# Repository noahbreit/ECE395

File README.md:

# ECE395
motor inverter project

# Start-Up Procedure
Step,Operation,Parameter,Value,Description
1,SAP,0,"1, 2, or 3",Set Motor Type 
2,SAP,4,3,Select Open-Loop Voltage Mode 
3,SAP,53,1,Enable Direct Velocity Mode 
4,SAP,47,[1000],Set Base Voltage/Duty Cycle 
5,SAP,124,[Speed],Set Target Velocity to Start

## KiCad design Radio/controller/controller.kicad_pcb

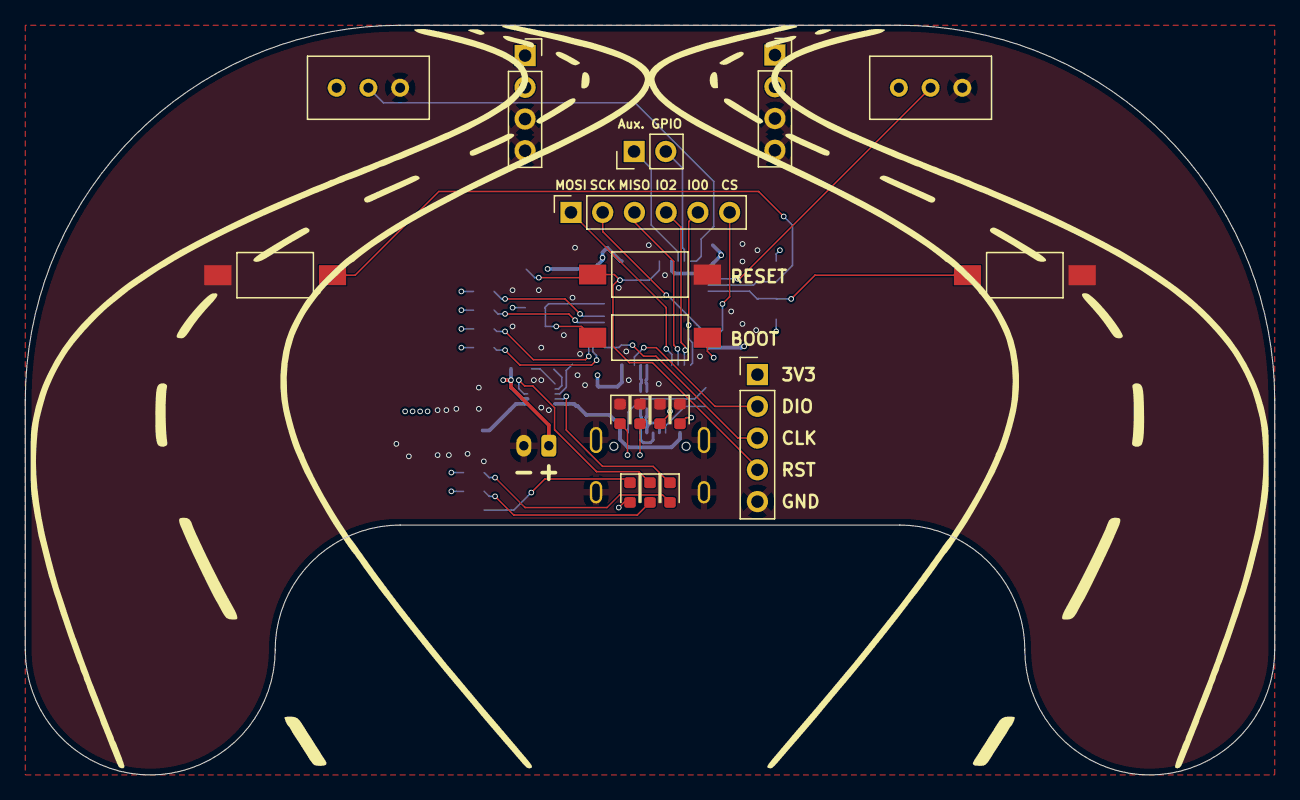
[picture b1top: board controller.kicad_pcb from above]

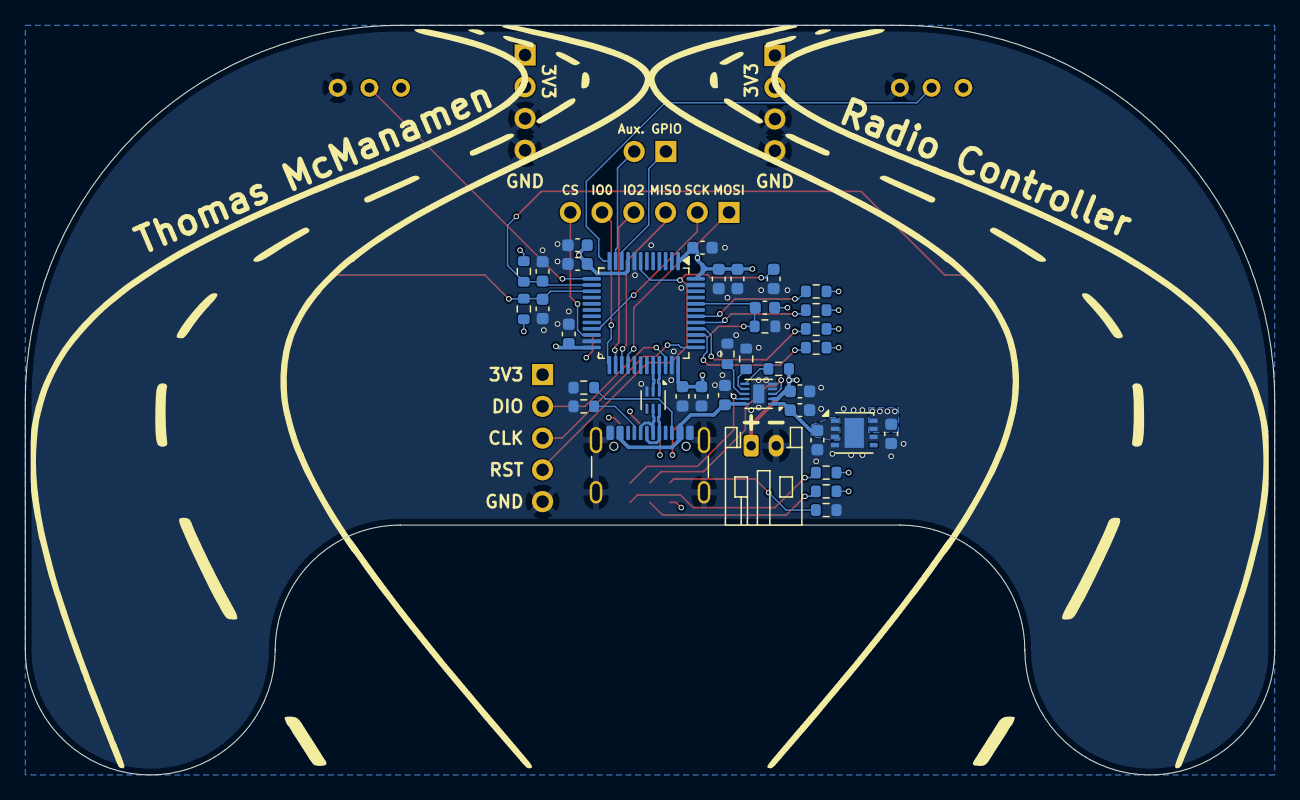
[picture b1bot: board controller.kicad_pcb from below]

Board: 4 copper layers, 100.0 x 60.0 mm, 56 parts (38 on the bottom side), 43 nets.

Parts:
C101: 10nF; C_0603_1608Metric
C102, C103, C104, C105, C109, C110, C111, C112: 100nF; C_0603_1608Metric
C106, C107, C114, C117: 1uF; C_0603_1608Metric
C108, C113, C115, C116: 10uF; C_0603_1608Metric
D101, D107: RED LED; LED_0603_1608Metric
D102, D106: ORANGE LED; LED_0603_1608Metric
D103, D105: GREEN LED; LED_0603_1608Metric
D104: BLUE LED; LED_0603_1608Metric
J101: Conn_01x06; PinSocket_1x06_P2.54mm_Vertical
J102: Conn_01x02; PinHeader_1x02_P2.54mm_Vertical
J103, J104: Conn_01x04; PinSocket_1x04_P2.54mm_Vertical
J105: USB4105-GF-A; USB_C_Receptacle_GCT_USB4105-xx-A_16P_TopMnt_Horizontal
J106: Conn_01x05; PinHeader_1x05_P2.54mm_Vertical
J107: S2B-PH-K-S; JST_PH_S2B-PH-K_1x02_P2.00mm_Horizontal
R101, R102, R103, R104, R110, R111, R115: 470; R_0603_1608Metric
R105, R108, R109, R114: 10k; R_0603_1608Metric
R106, R107: 5.1k; R_0603_1608Metric
R112: 18k; R_0603_1608Metric
R113: 604; R_0603_1608Metric
RV101, RV102: R_Potentiometer_US; Potentiometer_Bourns_3386C_Horizontal
SW101, SW102, SW103, SW104: SW_Push; SW_SPST_FSMSM
U101: STM32L412CBTx; LQFP-48_7x7mm_P0.5mm
U102: ECMF02-2AMX6; ST_UQFN-6L_1.5x1.7mm_P0.5mm
U103: MCP1727-3302xMF; DFN-8-1EP_3x3mm_P0.65mm_EP1.55x2.4mm
U104: BQ25185; Texas_DLH0010A_WSON-10-1EP_2.2x2mm_P0.4mm_EP0.9x1.5mm

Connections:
+3V3: C101.1, C102.1, C103.1, C104.1, C105.1, C106.1, C107.1, C108.1, C110.2, C115.1, D107.2 (A), J103.1, J103.2, J104.1, J104.2, J106.1, R108.1, R109.1, R110.2, R111.2, RV101.1, RV102.1, SW102.2, U101.1 (VBAT), U101.9 (VDDA), U101.24 (VDD), U101.36 (VDDUSB), U101.48 (VDD), U103.7 (Sense), U103.8 (Vout)
/ADC1: J102.1, U101.10 (PA0)
/ADC2: J102.2, U101.11 (PA1)
/BOOT0: C110.1, R105.1, SW102.1, U101.44 (PH3)
/BUTTON_1: C111.1, R108.2, SW103.1, U101.14 (PA4)
/BUTTON_2: C112.1, R109.2, SW104.1, U101.15 (PA5)
/CS: J101.6, U101.22 (PB11)
/D+: J105.A6 (D+), J105.B6 (D+), U102.6 (D+_out)
/D-: J105.A7 (D-), J105.B7 (D-), U102.5 (D-_out)
/GDO0: J101.5, U101.25 (PB12)
/GDO2: J101.4, U101.26 (PB13)
/LED_BLUE: R104.1, U101.42 (PB6)
/LED_GREEN: R103.1, U101.41 (PB5)
/LED_ORANGE: R102.1, U101.40 (PB4)
/LED_RED: R101.1, U101.39 (PB3)
/NRST: C109.1, J106.4, SW101.1, U101.7 (NRST)
/POT_1: RV101.2, U101.12 (PA2)
/POT_2: RV102.2, U101.13 (PA3)
/SPI_MISO: J101.3, U101.27 (PB14)
/SPI_MOSI: J101.1, U101.28 (PB15)
/SPI_SCK: J101.2, U101.21 (PB10)
/SWCLK: J106.3, U101.37 (PA14)
/SWDIO: J106.2, U101.34 (PA13)
/SYS_POWER: C113.1, C116.1, U103.1 (Vin), U103.2 (Vin), U103.3 (~SHDN), U104.1 (SYS)
/USB_D+: U101.33 (PA12), U102.1 (D+_in)
/USB_D-: U101.32 (PA11), U102.2 (D-_in)
/USB_POWER: C114.1, J105.A4 (VBUS), J105.A9 (VBUS), J105.B4 (VBUS), J105.B9 (VBUS), U104.10 (IN)
/VBAT: C117.1, J107.1, R114.2, U104.2 (BAT)
GND: C101.2, C102.2, C103.2, C104.2, C105.2, C106.2, C107.2, C108.2, C109.2, C111.2, C112.2, C113.2, C114.2, C115.2, C116.2, C117.2, D101.1 (K), D102.1 (K), D103.1 (K), D104.1 (K), J103.3, J103.4, J104.3, J104.4, J105.A1 (GND), J105.A12 (GND), J105.B1 (GND), J105.B12 (GND), J105.S1 (SHIELD), J106.5, J107.2, R105.2, R106.2, R107.2, R112.2, R113.2, R115.2, RV101.3, RV102.3, SW101.2, SW103.2, SW104.2, U101.8 (VSSA), U101.23 (VSS), U101.35 (VSS), U101.47 (VSS), U102.3 (GND), U103.4 (GND), U103.6 (Cdelay), U103.9 (GND), U104.4 (~CE), U104.5 (GND), U104.11 (EP)
unnamed: D101.2 (A), R101.2
unnamed: D102.2 (A), R102.2
unnamed: D103.2 (A), R103.2
unnamed: D104.2 (A), R104.2
unnamed: D105.2 (A), R110.1
unnamed: D105.1 (K), U104.9 (STAT1)
unnamed: D106.2 (A), R111.1
unnamed: D106.1 (K), U104.3 (STAT2)
unnamed: D107.1 (K), R115.1
unnamed: J105.A5 (CC1), R106.1
unnamed: J105.B5 (CC2), R107.1
unnamed: R112.1, U104.7 (ILIM/VSET)
unnamed: R113.1, U104.8 (ISET)
unnamed: R114.1, U104.6 (TS/MR)

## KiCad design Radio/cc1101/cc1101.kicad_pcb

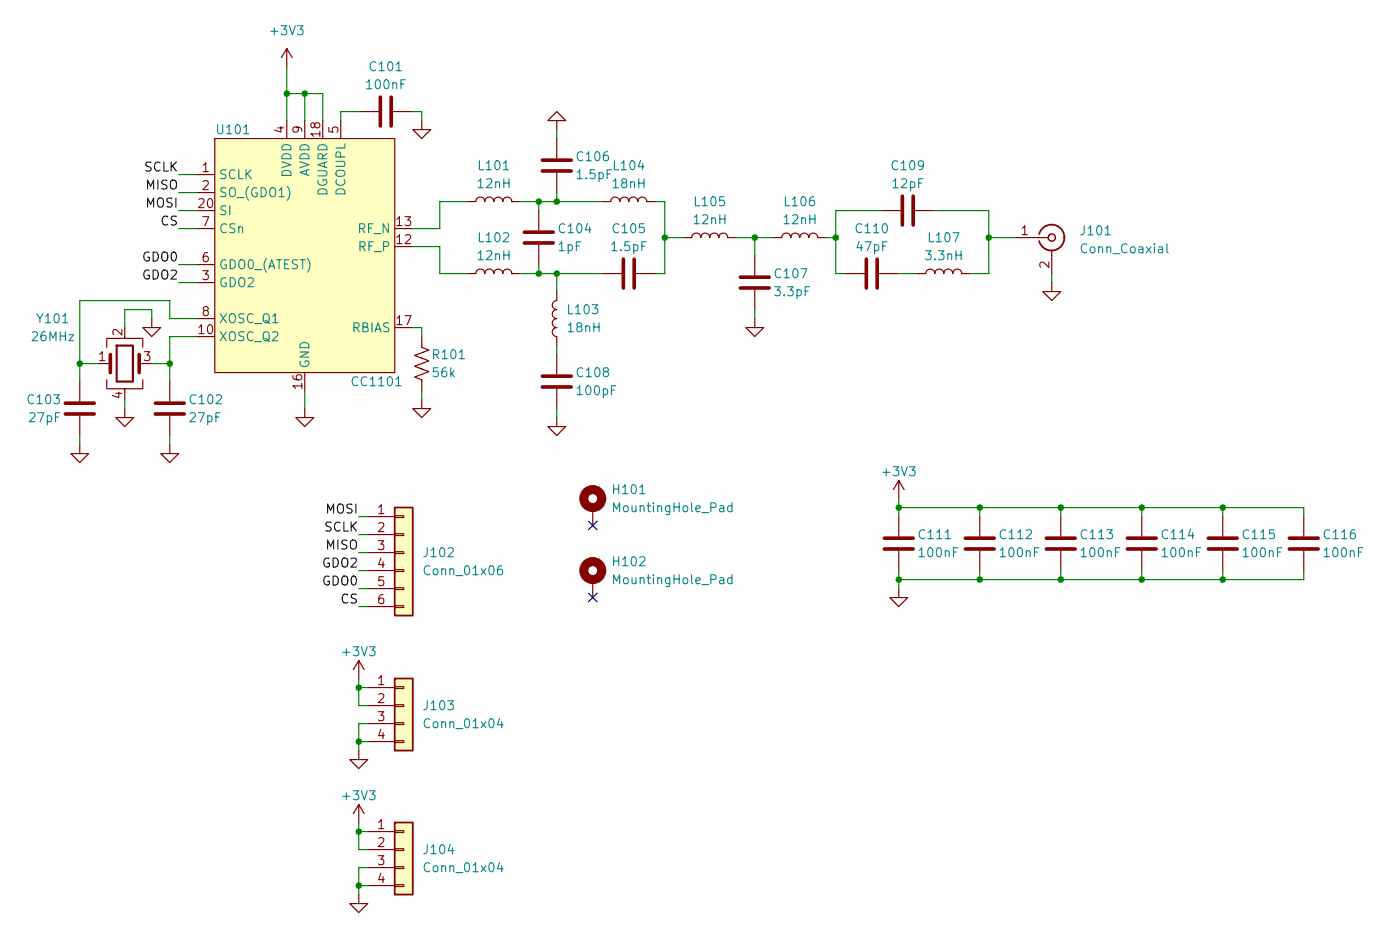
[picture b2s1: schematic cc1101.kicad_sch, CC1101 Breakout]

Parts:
C101, C111, C112, C113, C114, C115, C116: 100nF; C_0402_1005Metric
C102, C103: 27pF; C_0402_1005Metric
C104: 1pF; C_0402_1005Metric
C105, C106: 1.5pF; C_0402_1005Metric
C107: 3.3pF; C_0402_1005Metric
C108: 100pF; C_0402_1005Metric
C109: 12pF; C_0402_1005Metric
C110: 47pF; C_0402_1005Metric
H101, H102: MountingHole_Pad; MountingHole_2.2mm_M2_Pad_Via
J101: Conn_Coaxial; SMA_Molex_73251-2120_EdgeMount_Horizontal
J102: Conn_01x06; PinHeader_1x06_P2.54mm_Vertical
J103, J104: Conn_01x04; PinHeader_1x04_P2.54mm_Vertical
L101, L102, L105, L106: 12nH; L_0402_1005Metric
L103, L104: 18nH; L_0402_1005Metric
L107: 3.3nH; L_0402_1005Metric
R101: 56k; R_0402_1005Metric
U101: CC1101; Texas_RGP0020D_VQFN-20-1EP_4x4mm_P0.5mm_EP2.7x2.7mm
Y101: 26MHz; Crystal_SMD_3225-4Pin_3.2x2.5mm

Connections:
+3V3: C111.2, C112.2, C113.2, C114.2, C115.2, C116.2, J103.1, J103.2, J104.1, J104.2, U101.4 (DVDD), U101.9 (AVDD), U101.11 (AVDD), U101.14 (AVDD), U101.15 (AVDD), U101.18 (DGUARD)
/CS: J102.6, U101.7 (CSn)
/GDO0: J102.5, U101.6 (GDO0_(ATEST))
/GDO2: J102.4, U101.3 (GDO2)
/MISO: J102.3, U101.2 (SO_(GDO1))
/MOSI: J102.1, U101.20 (SI)
/SCLK: J102.2, U101.1 (SCLK)
GND: C101.2, C102.1, C103.1, C106.2, C107.1, C108.1, C111.1, C112.1, C113.1, C114.1, C115.1, C116.1, J101.2 (Ext), J103.3, J103.4, J104.3, J104.4, R101.2, U101.16 (GND), U101.19 (GND), U101.21 (PAD), Y101.2, Y101.4
unnamed: C104.1, C105.1, L102.2, L103.2
unnamed: C104.2, C106.1, L101.2, L104.1
unnamed: C105.2, L104.2, L105.1
unnamed: C107.2, L105.2, L106.1
unnamed: C108.2, L103.1
unnamed: C109.1, C110.1, L106.2
unnamed: C110.2, L107.1
unnamed: C109.2, J101.1 (In), L107.2
unnamed: C101.1, U101.5 (DCOUPL)
unnamed: R101.1, U101.17 (RBIAS)
unnamed: L101.1, U101.13 (RF_N)
unnamed: L102.1, U101.12 (RF_P)
unnamed: C103.2, U101.8 (XOSC_Q1), Y101.1
unnamed: C102.2, U101.10 (XOSC_Q2), Y101.3

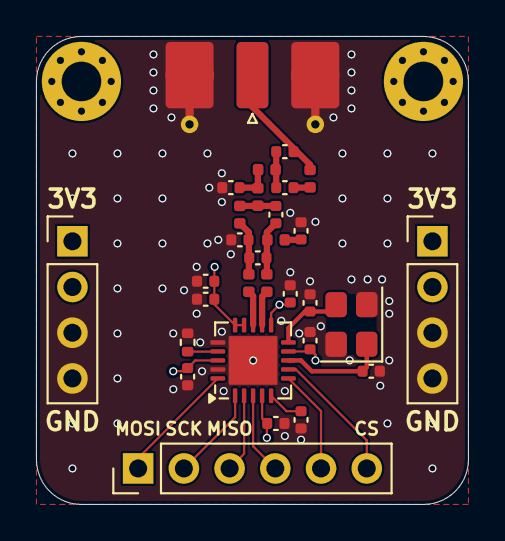
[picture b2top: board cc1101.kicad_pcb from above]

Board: 4 copper layers, 24.0 x 26.0 mm, 32 parts (0 on the bottom side), 22 nets.

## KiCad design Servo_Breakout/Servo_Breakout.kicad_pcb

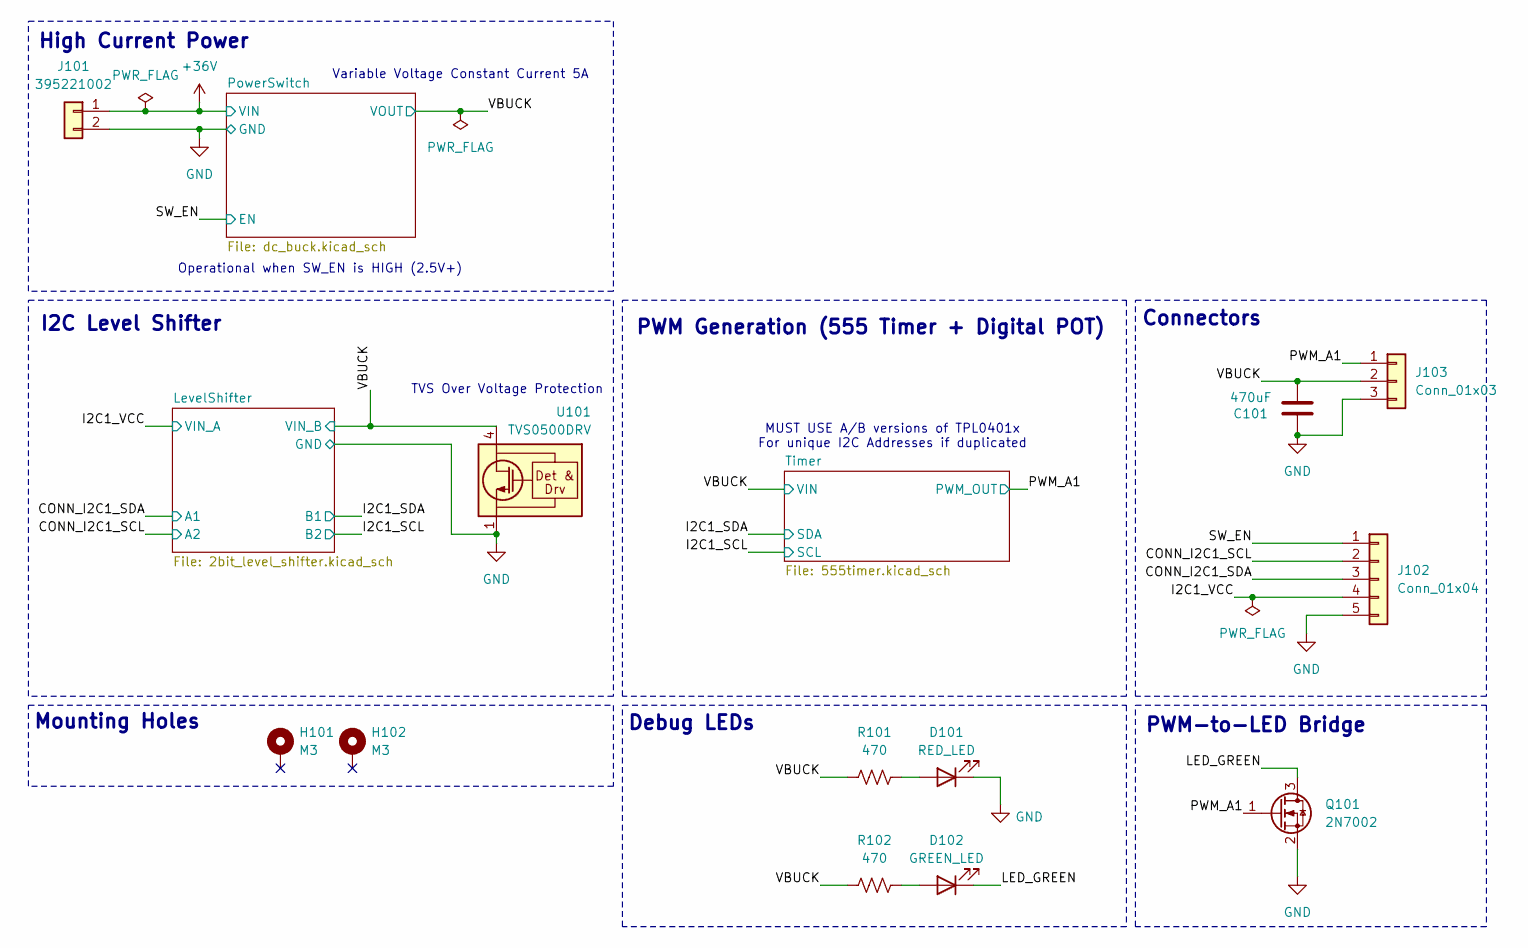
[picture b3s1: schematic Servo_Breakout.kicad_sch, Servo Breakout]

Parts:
C101: 470uF; C_Radial_D10.0mm_H20.0mm_P5.00mm
D101: RED_LED; LED_0603_1608Metric
D102: GREEN_LED; LED_0603_1608Metric
H101, H102: M3; MountingHole_3.2mm_M3_Pad_Via
J101: 395221002; Molex_39522-002_1x02_P5.00mm_Horizontal
J102: Conn_01x04; PinHeader_1x05_P2.54mm_Vertical
J103: Conn_01x03; PinHeader_1x03_P2.54mm_Vertical
Q101: 2N7002; SOT-23
R101, R102: 470; R_0805_2012Metric_Pad1.20x1.40mm_HandSolder
U101: TVS0500DRV; WSON-6-1EP_2x2mm_P0.65mm_EP1x1.6mm

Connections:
+36V: J101.1; also elsewhere on the board
/CONN_I2C1_SCL: J102.2; also elsewhere on the board
/CONN_I2C1_SDA: J102.3; also elsewhere on the board
/I2C1_VCC: J102.4; also elsewhere on the board
/LED_GREEN: D102.1 (K), Q101.3 (D)
/PWM_A1: J103.1, Q101.1 (G); also elsewhere on the board
/SW_EN: J102.1; also elsewhere on the board
/VBUCK: C101.1, J103.2, R101.1, R102.1, U101.4 (IN), U101.5 (IN), U101.6 (IN); also elsewhere on the board
GND: C101.2, D101.1 (K), J101.2, J102.5, J103.3, Q101.2 (S), U101.1 (GND), U101.2 (GND), U101.3 (GND), U101.7 (GND); also elsewhere on the board
unnamed: D101.2 (A), R101.2
unnamed: D102.2 (A), R102.2

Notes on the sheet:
TVS Over Voltage Protection
Operational when SW_EN is HIGH (2.5V+)
High Current Power
Connectors
Debug LEDs
PWM Generation (555 Timer + Digital POT)
Variable Voltage Constant Current 5A
Mounting Holes
I2C Level Shifter
MUST USE A/B versions of TPL0401x For unique I2C Addresses if duplicated
PWM-to-LED Bridge

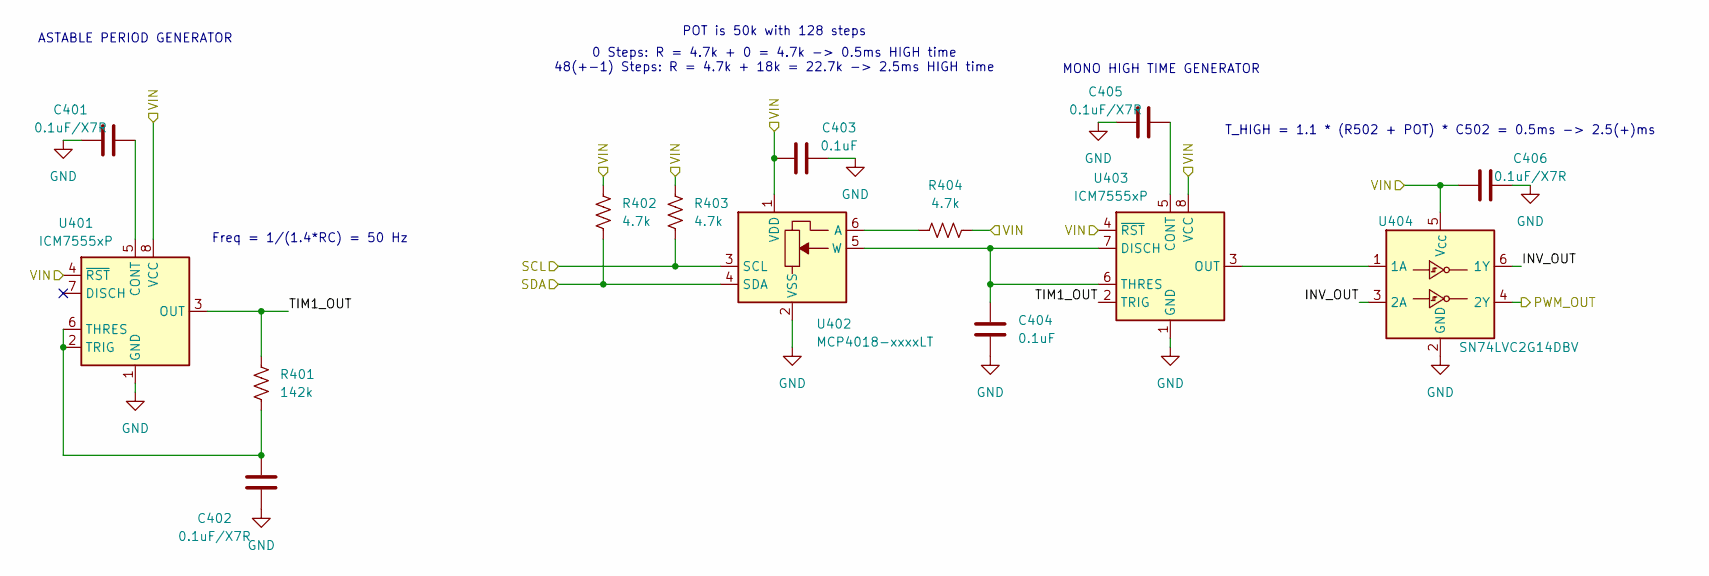
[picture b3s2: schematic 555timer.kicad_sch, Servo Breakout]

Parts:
C401, C402, C405, C406: 0.1uF/X7R; C_0805_2012Metric_Pad1.18x1.45mm_HandSolder
C403, C404: 0.1uF; C_0805_2012Metric_Pad1.18x1.45mm_HandSolder
R401: 142k; R_0805_2012Metric_Pad1.20x1.40mm_HandSolder
R402, R403, R404: 4.7k; R_0805_2012Metric_Pad1.20x1.40mm_HandSolder
U401, U403: ICM7555xP; DIP-8_W7.62mm
U402: MCP4018-xxxxLT; SOT-363_SC-70-6
U404: SN74LVC2G14DBV; SOT-23-6

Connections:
/I2C1_SCL: R403.2, U402.3 (SCL); also elsewhere on the board
/I2C1_SDA: R402.2, U402.4 (SDA); also elsewhere on the board
/PWM_A1: U404.4 (2Y); also elsewhere on the board
/Timer/INV_OUT: U404.3 (2A), U404.6 (1Y)
/Timer/TIM1_OUT: R401.1, U401.3 (OUT), U403.2 (TRIG)
/VBUCK: C403.1, C406.1, R402.1, R403.1, R404.2, U401.4 (~RST), U401.8 (VCC), U402.1 (VDD), U403.4 (~RST), U403.8 (VCC), U404.5 (V_{CC}); also elsewhere on the board
GND: C401.2, C402.2, C403.2, C404.2, C405.2, C406.2, U401.1 (GND), U402.2 (VSS), U403.1 (GND), U404.2 (GND); also elsewhere on the board
unnamed: C401.1, U401.5 (CONT)
unnamed: C402.1, R401.2, U401.2 (TRIG), U401.6 (THRES)
unnamed: R404.1, U402.6 (A)
unnamed: C404.1, U402.5 (W), U403.6 (THRES), U403.7 (DISCH)
unnamed: C405.1, U403.5 (CONT)
unnamed: U403.3 (OUT), U404.1 (1A)

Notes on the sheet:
ASTABLE PERIOD GENERATOR
Freq = 1/(1.4*RC) = 50 Hz
POT is 50k with 128 steps
T_HIGH = 1.1 * (R502 + POT) * C502 = 0.5ms -> 2.5(+)ms
0 Steps: R = 4.7k + 0 = 4.7k -> 0.5ms HIGH time 48(+-1) Steps: R = 4.7k + 18k = 22.7k -> 2.5ms HIGH time
MONO HIGH TIME GENERATOR

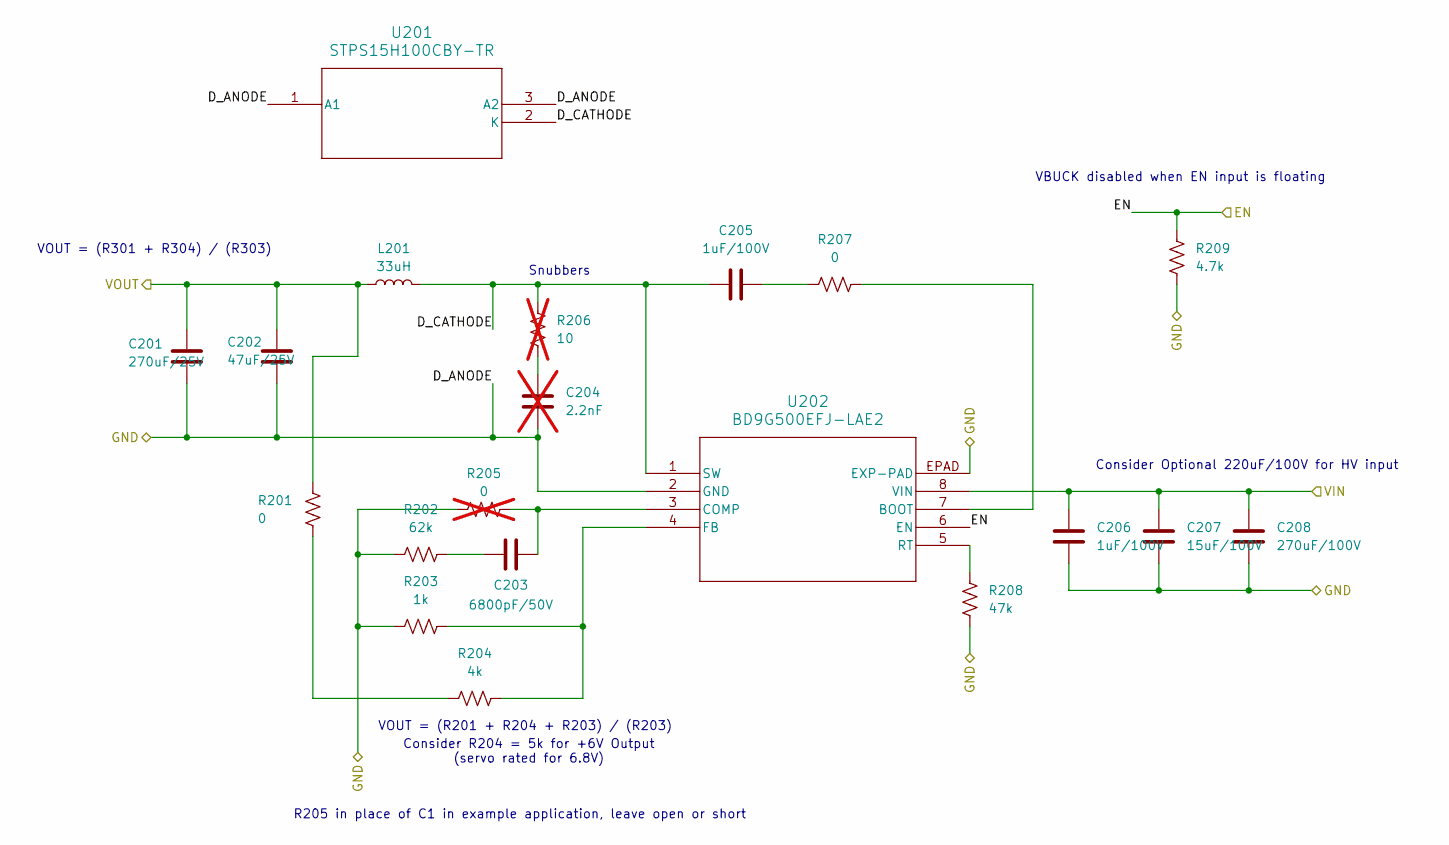
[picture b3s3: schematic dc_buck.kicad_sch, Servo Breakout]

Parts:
C201: 270uF/25V; CP_Radial_D10.0mm_P5.00mm
C202: 47uF/25V; C_2220_5750Metric_Pad1.97x5.40mm_HandSolder
C203: 6800pF/50V; C_0805_2012Metric_Pad1.18x1.45mm_HandSolder
C204: 2.2nF; C_0805_2012Metric_Pad1.18x1.45mm_HandSolder; not fitted
C205, C206: 1uF/100V; C_0805_2012Metric_Pad1.18x1.45mm_HandSolder
C207: 15uF/100V; C_2220_5750Metric_Pad1.97x5.40mm_HandSolder
C208: 270uF/100V; CP_Radial_D16.0mm_P7.50mm
L201: 33uH; L_Vishay_IHLP-3232
R201, R207: 0; R_0805_2012Metric_Pad1.20x1.40mm_HandSolder
R202: 62k; R_0805_2012Metric_Pad1.20x1.40mm_HandSolder
R203: 1k; R_0805_2012Metric_Pad1.20x1.40mm_HandSolder
R204: 4k; R_0805_2012Metric_Pad1.20x1.40mm_HandSolder
R205: 0; R_0805_2012Metric_Pad1.20x1.40mm_HandSolder; not fitted
R206: 10; R_0805_2012Metric_Pad1.20x1.40mm_HandSolder; not fitted
R208: 47k; R_0805_2012Metric_Pad1.20x1.40mm_HandSolder
R209: 4.7k; R_0805_2012Metric_Pad1.20x1.40mm_HandSolder
U201: STPS15H100CBY-TR
U202: BD9G500EFJ-LAE2; SOIC8_BD9G500EFJ-LAE2_ROM

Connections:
+36V: C206.1, C207.1, C208.1, U202.8 (VIN); also elsewhere on the board
/PowerSwitch/D_CATHODE: C205.1, L201.2, R206.1, U201.2 (K), U202.1 (SW)
/SW_EN: R209.2, U202.6 (EN); also elsewhere on the board
/VBUCK: C201.1, C202.1, L201.1, R201.1; also elsewhere on the board
GND: C201.2, C202.2, C204.2, C206.2, C207.2, C208.2, R202.1, R203.1, R205.1, R208.2, R209.1, U201.1 (A1), U201.3 (A2), U202.2 (GND), U202.EPAD (EXP-PAD); also elsewhere on the board
unnamed: C203.1, R202.2
unnamed: C204.1, R206.2
unnamed: C205.2, R207.1
unnamed: R201.2, R204.1
unnamed: R207.2, U202.7 (BOOT)
unnamed: C203.2, R205.2, U202.3 (COMP)
unnamed: R203.2, R204.2, U202.4 (FB)
unnamed: R208.1, U202.5 (RT)

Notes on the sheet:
Snubbers
Consider Optional 220uF/100V for HV input
VOUT = (R301 + R304) / (R303)
Consider R204 = 5k for +6V Output (servo rated for 6.8V)
R205 in place of C1 in example application, leave open or short
VBUCK disabled when EN input is floating
VOUT = (R201 + R204 + R203) / (R203)

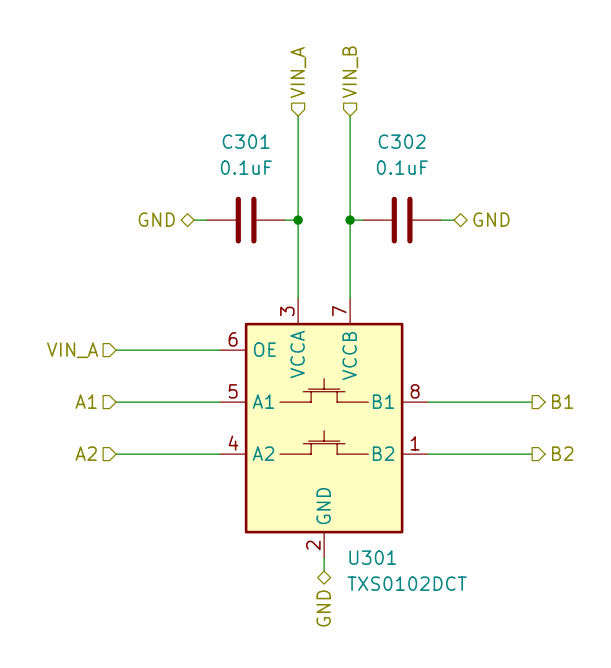
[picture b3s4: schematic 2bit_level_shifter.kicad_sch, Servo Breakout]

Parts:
C301, C302: 0.1uF; C_0805_2012Metric_Pad1.18x1.45mm_HandSolder
U301: TXS0102DCT; SSOP-8_2.95x2.8mm_P0.65mm

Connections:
/CONN_I2C1_SCL: U301.4 (A2); also elsewhere on the board
/CONN_I2C1_SDA: U301.5 (A1); also elsewhere on the board
/I2C1_SCL: U301.1 (B2); also elsewhere on the board
/I2C1_SDA: U301.8 (B1); also elsewhere on the board
/I2C1_VCC: C301.2, U301.3 (VCCA), U301.6 (OE); also elsewhere on the board
/VBUCK: C302.1, U301.7 (VCCB); also elsewhere on the board
GND: C301.1, C302.2, U301.2 (GND); also elsewhere on the board

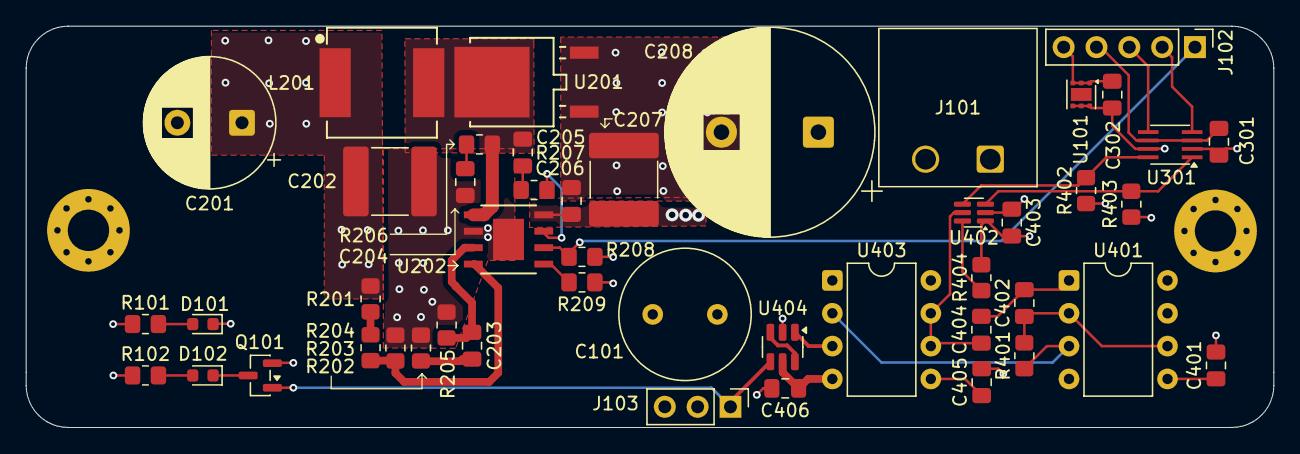
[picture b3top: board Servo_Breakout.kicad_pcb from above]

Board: 4 copper layers, 96.5 x 31.0 mm, 49 parts (0 on the bottom side), 30 nets.

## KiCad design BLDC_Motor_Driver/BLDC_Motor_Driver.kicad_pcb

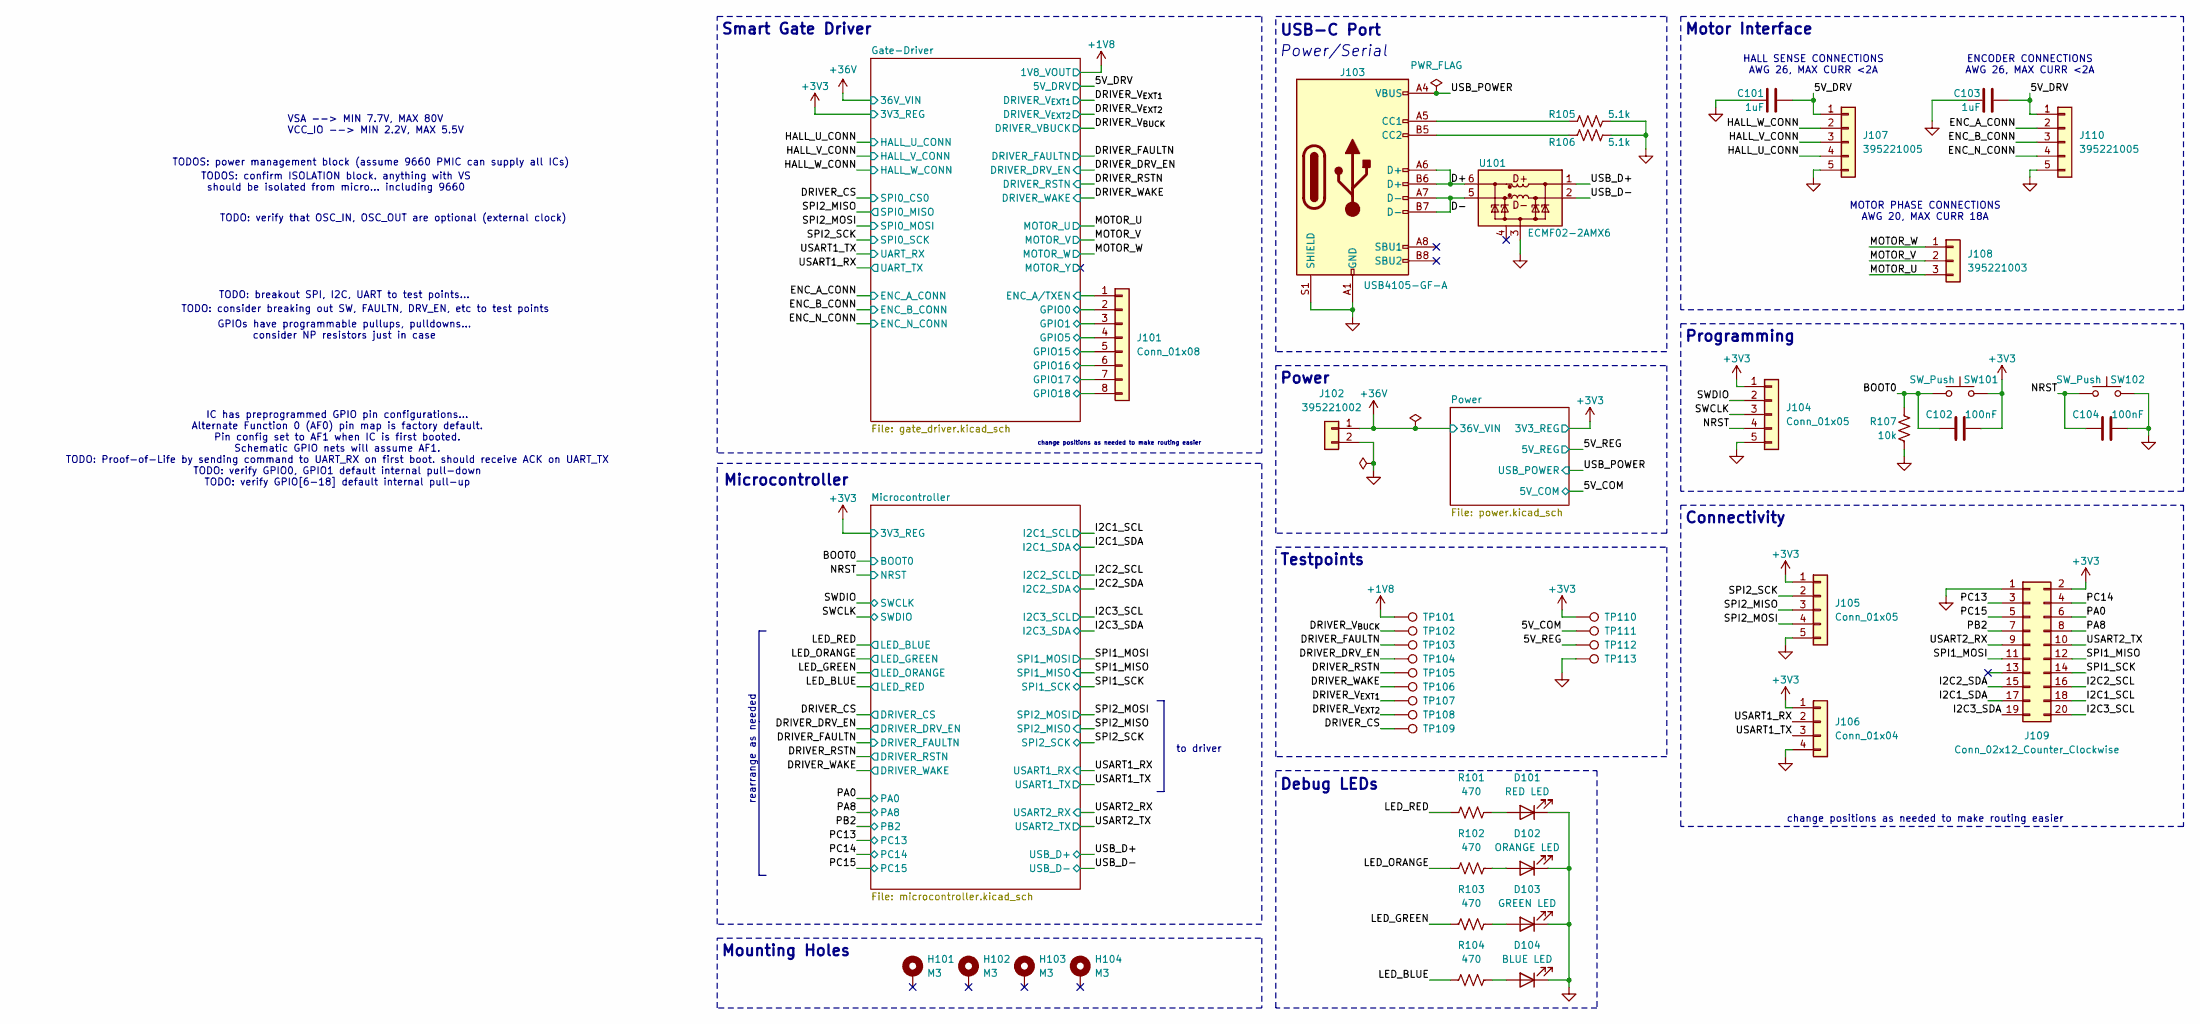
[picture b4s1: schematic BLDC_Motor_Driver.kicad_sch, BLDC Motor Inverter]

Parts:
C101, C103: 1uF; C_0603_1608Metric
C102, C104: 100nF; C_0603_1608Metric
D101: RED LED; LED_0603_1608Metric
D102: ORANGE LED; LED_0603_1608Metric
D103: GREEN LED; LED_0603_1608Metric
D104: BLUE LED; LED_0603_1608Metric
H101, H102, H103, H104: M3; MountingHole_3.2mm_M3_Pad_Via
J101: Conn_01x08; PinHeader_1x08_P2.54mm_Vertical
J102: 395221002; Molex_39522-002_1x02_P5.00mm_Horizontal
J103: USB4105-GF-A; USB_C_Receptacle_GCT_USB4105-xx-A_16P_TopMnt_Horizontal
J104, J105: Conn_01x05; PinHeader_1x05_P2.54mm_Vertical
J106: Conn_01x04; PinHeader_1x04_P2.54mm_Vertical
J107, J110: 395221005; Molex_39522-005_1x05_P5.00mm_Horizontal
J108: 395221003; Molex_39522-003_1x03_P5.00mm_Horizontal
J109: Conn_02x12_Counter_Clockwise; PinHeader_2x10_P2.54mm_Vertical
R101, R102, R103, R104: 470; R_0603_1608Metric
R105, R106: 5.1k; R_0603_1608Metric
R107: 10k; R_0603_1608Metric
SW101, SW102: SW_Push; SW_SPST_FSMSM
TP101, TP102, TP103, TP104, TP105, TP106, TP107, TP108, TP109: TestPoint; TestPoint_THTPad_D2.0mm_Drill1.0mm
TP110, TP111, TP112, TP113: TestPoint_THTPad_D2.0mm_Drill1.0mm
U101: ECMF02-2AMX6; ST_UQFN-6L_1.5x1.7mm_P0.5mm

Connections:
+1V8: TP101.1; also elsewhere on the board
+3V3: C102.2, J104.1, J105.1, J106.1, J109.2, SW101.2, TP110.1; also elsewhere on the board
+36V: J102.1; also elsewhere on the board
/5V_COM: TP111.1; also elsewhere on the board
/5V_DRV: C101.1, C103.1, J107.1, J110.1, TP107.1; also elsewhere on the board
/5V_REG: TP112.1; also elsewhere on the board
/BOOT0: C102.1, R107.1, SW101.1; also elsewhere on the board
/D+: J103.A6 (D+), J103.B6 (D+), U101.6 (D+_out)
/D-: J103.A7 (D-), J103.B7 (D-), U101.5 (D-_out)
/DRIVER_CS: TP109.1; also elsewhere on the board
/DRIVER_DRV_EN: TP104.1; also elsewhere on the board
/DRIVER_FAULTN: TP103.1; also elsewhere on the board
/DRIVER_RSTN: TP105.1; also elsewhere on the board
/DRIVER_V_{BUCK}: TP102.1; also elsewhere on the board
/DRIVER_V_{EXT2}: TP108.1; also elsewhere on the board
/DRIVER_WAKE: TP106.1; also elsewhere on the board
/ENC_A_CONN: J110.2; also elsewhere on the board
/ENC_B_CONN: J110.3; also elsewhere on the board
/ENC_N_CONN: J110.4; also elsewhere on the board
/Gate-Driver/ENC_A/TXEN: J101.1; also elsewhere on the board
/Gate-Driver/GPIO0: J101.2; also elsewhere on the board
/Gate-Driver/GPIO1: J101.3; also elsewhere on the board
/Gate-Driver/GPIO5: J101.4; also elsewhere on the board
/Gate-Driver/GPIO15: J101.5; also elsewhere on the board
/Gate-Driver/GPIO16: J101.6; also elsewhere on the board
/Gate-Driver/GPIO17: J101.7; also elsewhere on the board
/Gate-Driver/GPIO18: J101.8; also elsewhere on the board
/HALL_U_CONN: J107.4; also elsewhere on the board
/HALL_V_CONN: J107.3; also elsewhere on the board
/HALL_W_CONN: J107.2; also elsewhere on the board
/I2C1_SCL: J109.18; also elsewhere on the board
/I2C1_SDA: J109.17; also elsewhere on the board
/I2C2_SCL: J109.16; also elsewhere on the board
/I2C2_SDA: J109.15; also elsewhere on the board
/I2C3_SCL: J109.20; also elsewhere on the board
/I2C3_SDA: J109.19; also elsewhere on the board
/LED_BLUE: R104.1; also elsewhere on the board
/LED_GREEN: R103.1; also elsewhere on the board
/LED_ORANGE: R102.1; also elsewhere on the board
/LED_RED: R101.1; also elsewhere on the board
/MOTOR_U: J108.3; also elsewhere on the board
/MOTOR_V: J108.2; also elsewhere on the board
/MOTOR_W: J108.1; also elsewhere on the board
/NRST: C104.1, J104.4, SW102.1; also elsewhere on the board
/PA0: J109.6; also elsewhere on the board
/PA8: J109.8; also elsewhere on the board
/PB2: J109.7; also elsewhere on the board
/PC13: J109.3; also elsewhere on the board
/PC14: J109.4; also elsewhere on the board
/PC15: J109.5; also elsewhere on the board
/SPI1_MISO: J109.12; also elsewhere on the board
/SPI1_MOSI: J109.11; also elsewhere on the board
/SPI1_SCK: J109.14; also elsewhere on the board
/SPI2_MISO: J105.3; also elsewhere on the board
/SPI2_MOSI: J105.4; also elsewhere on the board
/SPI2_SCK: J105.2; also elsewhere on the board
/SWCLK: J104.3; also elsewhere on the board
/SWDIO: J104.2; also elsewhere on the board
/USART1_RX: J106.2; also elsewhere on the board
/USART1_TX: J106.3; also elsewhere on the board
/USART2_RX: J109.9; also elsewhere on the board
/USART2_TX: J109.10; also elsewhere on the board
/USB_D+: U101.1 (D+_in); also elsewhere on the board
/USB_D-: U101.2 (D-_in); also elsewhere on the board
/USB_POWER: J103.A4 (VBUS), J103.A9 (VBUS), J103.B4 (VBUS), J103.B9 (VBUS); also elsewhere on the board
GND: C101.2, C103.2, C104.2, D101.1 (K), D102.1 (K), D103.1 (K), D104.1 (K), J102.2, J103.A1 (GND), J103.A12 (GND), J103.B1 (GND), J103.B12 (GND), J103.S1 (SHIELD), J104.5, J105.5, J106.4, J107.5, J109.1, J110.5, R105.2, R106.2, R107.2, SW102.2, TP113.1, U101.3 (GND); also elsewhere on the board
unnamed: D101.2 (A), R101.2
unnamed: D102.2 (A), R102.2
unnamed: D103.2 (A), R103.2
unnamed: D104.2 (A), R104.2
unnamed: J103.A5 (CC1), R105.1
unnamed: J103.B5 (CC2), R106.1

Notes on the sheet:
TODO: consider breaking out SW, FAULTN, DRV_EN, etc to test points
Motor Interface
VSA --> MIN 7.7V, MAX 80V VCC_IO --> MIN 2.2V, MAX 5.5V
TODOS: confirm ISOLATION block. anything with VS should be isolated from micro... including 9660
Microcontroller
ENCODER CONNECTIONS AWG 26, MAX CURR <2A
USB-C Port
TODOS: power management block (assume 9660 PMIC can supply all ICs)
rearrange as needed
Connectivity
Mounting Holes
Power/Serial
MOTOR PHASE CONNECTIONS AWG 20, MAX CURR 18A
TODO: verify that OSC_IN, OSC_OUT are optional (external clock)
Testpoints
to driver
change positions as needed to make routing easier
HALL SENSE CONNECTIONS AWG 26, MAX CURR <2A
Debug LEDs
Power
Programming
IC has preprogrammed GPIO pin configurations... Alternate Function 0 (AF0) pin map is factory default. Pin config set to AF1 when IC is first booted. Schematic GPIO nets will assume AF1. TODO: Proof-of-Life by sending command to UART_RX on first boot. should receive ACK on UART_TX TODO: verify GPIO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
TODO: breakout SPI, I2C, UART to test points...
GPIOs have programmable pullups, pulldowns... consider NP resistors just in case
Smart Gate Driver

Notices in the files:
bldc-sw-test/Core/Src/main.c:
Copyright (c) 2026 STMicroelectronics.
All rights reserved.
This software is licensed under terms that can be found in the LICENSE file
